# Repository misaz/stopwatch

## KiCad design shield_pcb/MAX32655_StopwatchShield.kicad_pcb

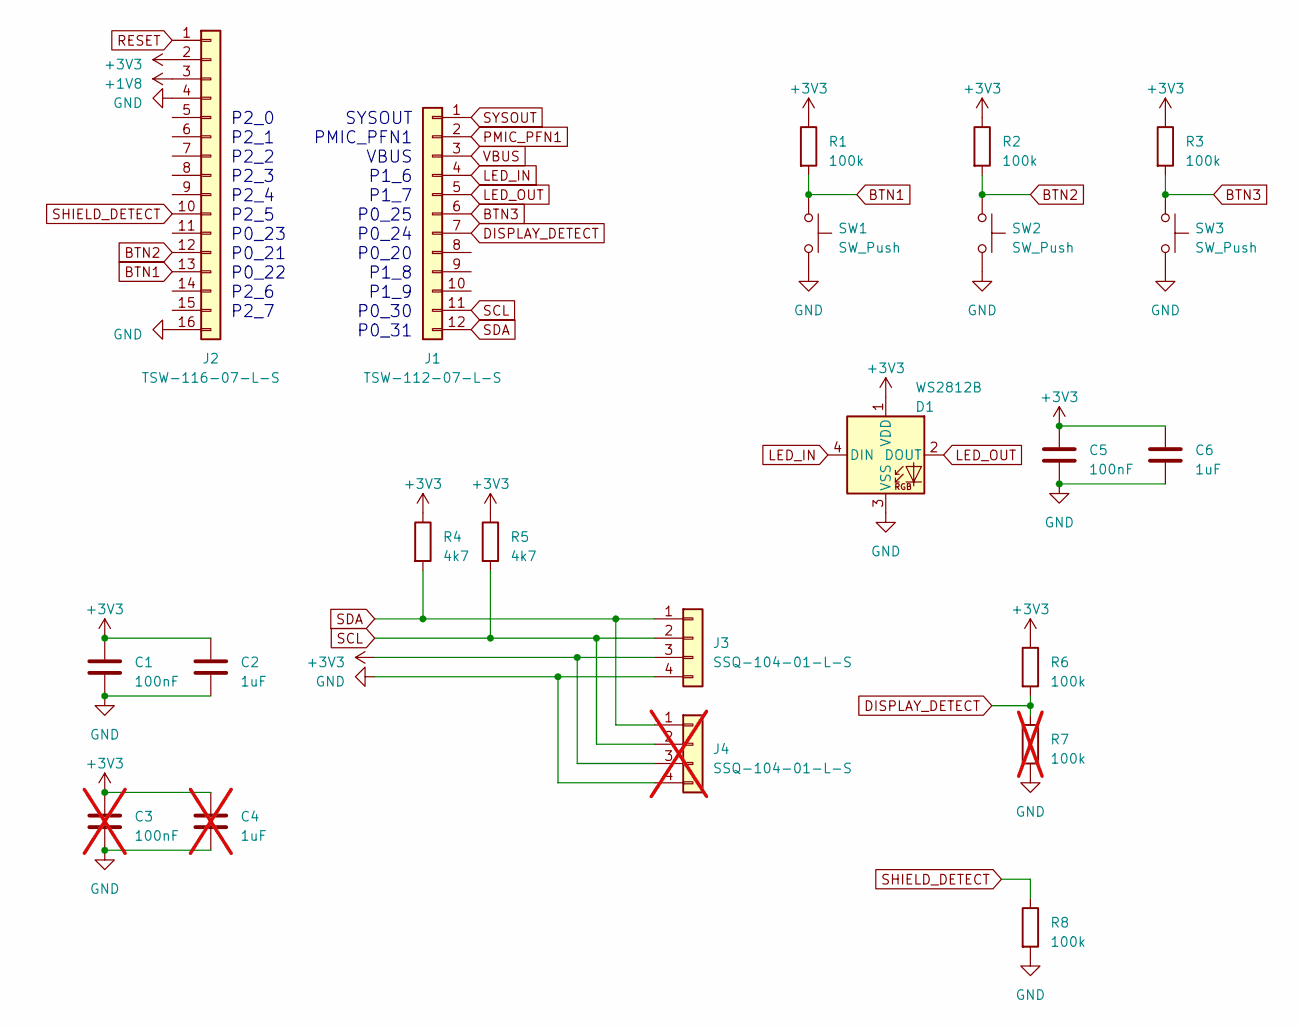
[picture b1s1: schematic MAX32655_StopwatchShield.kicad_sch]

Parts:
C1, C5: 100nF; C_0603_1608Metric_Pad1.08x0.95mm_HandSolder
C2, C6: 1uF; C_0603_1608Metric_Pad1.08x0.95mm_HandSolder
C3: 100nF; C_0603_1608Metric_Pad1.08x0.95mm_HandSolder; not fitted
C4: 1uF; C_0603_1608Metric_Pad1.08x0.95mm_HandSolder; not fitted
D1: WS2812B; LED_WS2812B_PLCC4_5.0x5.0mm_P3.2mm
J1: TSW-112-07-L-S; PinHeader_1x12_P2.54mm_Vertical
J2: TSW-116-07-L-S; PinHeader_1x16_P2.54mm_Vertical
J3: SSQ-104-01-L-S; PinSocket_1x04_P2.54mm_Vertical_SMD_Pin1Left
J4: SSQ-104-01-L-S; PinSocket_1x04_P2.54mm_Vertical_SMD_Pin1Left; not fitted
R1, R2, R3, R6, R8: 100k; R_0603_1608Metric_Pad0.98x0.95mm_HandSolder
R4, R5: 4k7; R_0603_1608Metric_Pad0.98x0.95mm_HandSolder
R7: 100k; R_0603_1608Metric_Pad0.98x0.95mm_HandSolder; not fitted
SW1, SW2, SW3: SW_Push; SW_Push_1P1T_NO_6x6mm_H9.5mm

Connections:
+1V8: J2.3
+3V3: C1.1, C2.1, C3.1, C4.1, C5.1, C6.1, D1.1 (VDD), J2.2, J3.3, J4.3, R1.1, R2.1, R3.1, R4.1, R5.1, R6.1
BTN1: J2.13, R1.2, SW1.1
BTN2: J2.12, R2.2, SW2.1
BTN3: J1.6, R3.2, SW3.1
DISPLAY_DETECT: J1.7, R6.2, R7.1
GND: C1.2, C2.2, C3.2, C4.2, C5.2, C6.2, D1.3 (VSS), J2.4, J2.16, J3.4, J4.4, R7.2, R8.2, SW1.2, SW2.2, SW3.2
LED_IN: D1.4 (DIN), J1.4
LED_OUT: D1.2 (DOUT), J1.5
PMIC_PFN1: J1.2
RESET: J2.1
SCL: J1.11, J3.2, J4.2, R5.2
SDA: J1.12, J3.1, J4.1, R4.2
SHIELD_DETECT: J2.10, R8.1
SYSOUT: J1.1
VBUS: J1.3

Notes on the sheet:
SYSOUT PMIC_PFN1 VBUS P1_6 P1_7 P0_25 P0_24 P0_20 P1_8 P1_9 P0_30 P0_31
P2_0 P2_1 P2_2 P2_3 P2_4 P2_5 P0_23 P0_21 P0_22 P2_6 P2_7

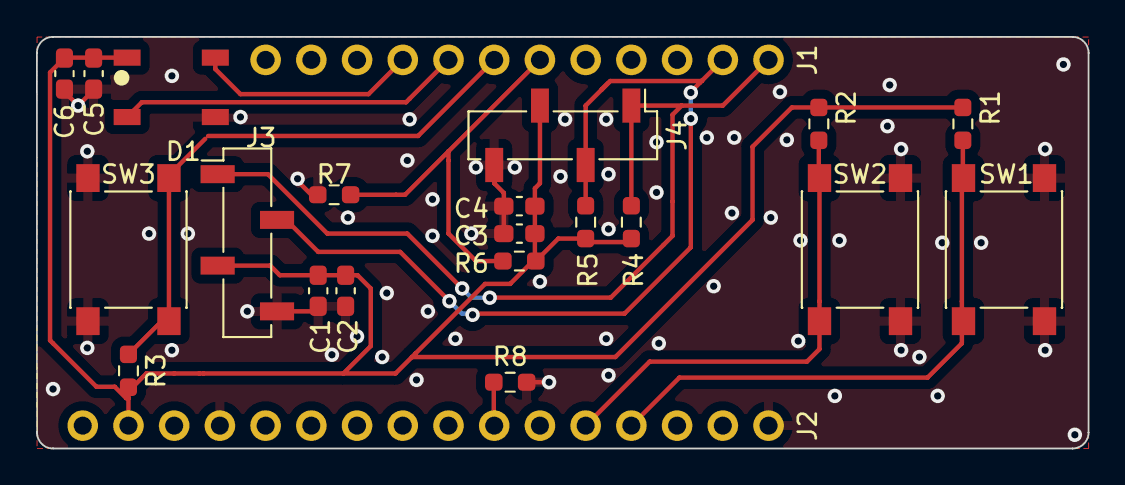
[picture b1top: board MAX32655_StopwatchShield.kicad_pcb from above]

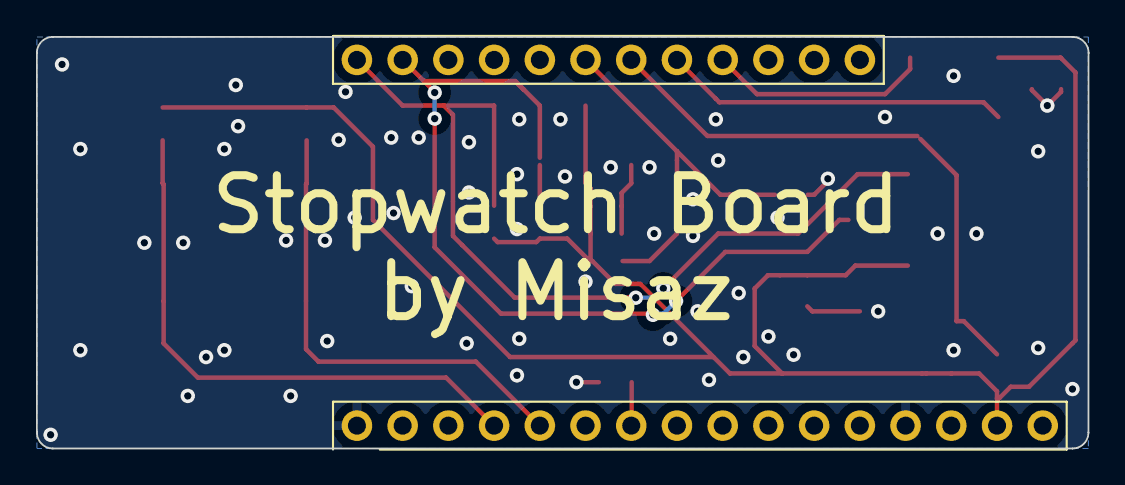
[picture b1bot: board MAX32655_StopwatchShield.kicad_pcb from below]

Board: 2 copper layers, 58.4 x 22.9 mm, 22 parts (2 on the bottom side), 11 nets.

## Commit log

2023-03-21 Initial state (fit demo)
2023-03-21 refactoring main
2023-03-21 cleanup completion
2023-03-21 ignroed flash.log file
2023-03-21 structures cleanup
2023-03-22 added service and first characteristics
2023-03-22 added elapsed characteristics
2023-03-22 added all remaining stopwatch characterististics
2023-03-22 added characteristics name descriptions
2023-03-24 work on display driver
2023-03-24 completed display driver implementation and basic GUI driver.
2023-03-24 added button and time driver
2023-03-25 progress on display GUI
2023-03-25 progress on GUI and basic stopwatch implemented
2023-03-26 implemented BLE icon logic
2023-03-26 removed display debugging messages
2023-03-26 added support for laps top GUI
2023-03-26 added support for printing spaces
2023-03-26 fixed stopping lap
2023-03-31 refactoring, information propagation ot BLE, fixed timer constant
2023-03-31 added RGB LED driver and logic
2023-03-31 removed unused code in ws2812b driver.
2023-03-31 fixed missing last gpio state on RGB led
2023-03-31 Completed fuel gauge indication and improved RGB LED stability
2023-04-01 added menu to GUI, basic support for powering down MCU
2023-04-01 Added support for powering device off (go to standby mode)
2023-04-01 fixed rendering changes when menu is open
2023-04-01 mvoed firmware to own folder
2023-04-01 windows_app scanning for device and connection estabilishment + GATT notification registration.
2023-04-01 addded support for showing time and lap infomration in windows GUI app
2023-04-03 device rename
2023-04-03 Improved reliability of turning display off.
2023-04-03 removed initial high intensity green led blink
2023-04-03 Refactored time formatting in GUI, reordered menu items, improved edge cases in GUI operation hadnling when connection is unexpectedly lost.
2023-04-03 Improved windows app GUI
2023-04-04 renamed searched device in BLE adv watcher
2023-04-04 changed memory pool settings, firmware refactor
2023-04-04 added stopwatch shield PCB kicad project
